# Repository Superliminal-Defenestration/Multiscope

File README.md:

Schematic Image

KiCad 3D Render

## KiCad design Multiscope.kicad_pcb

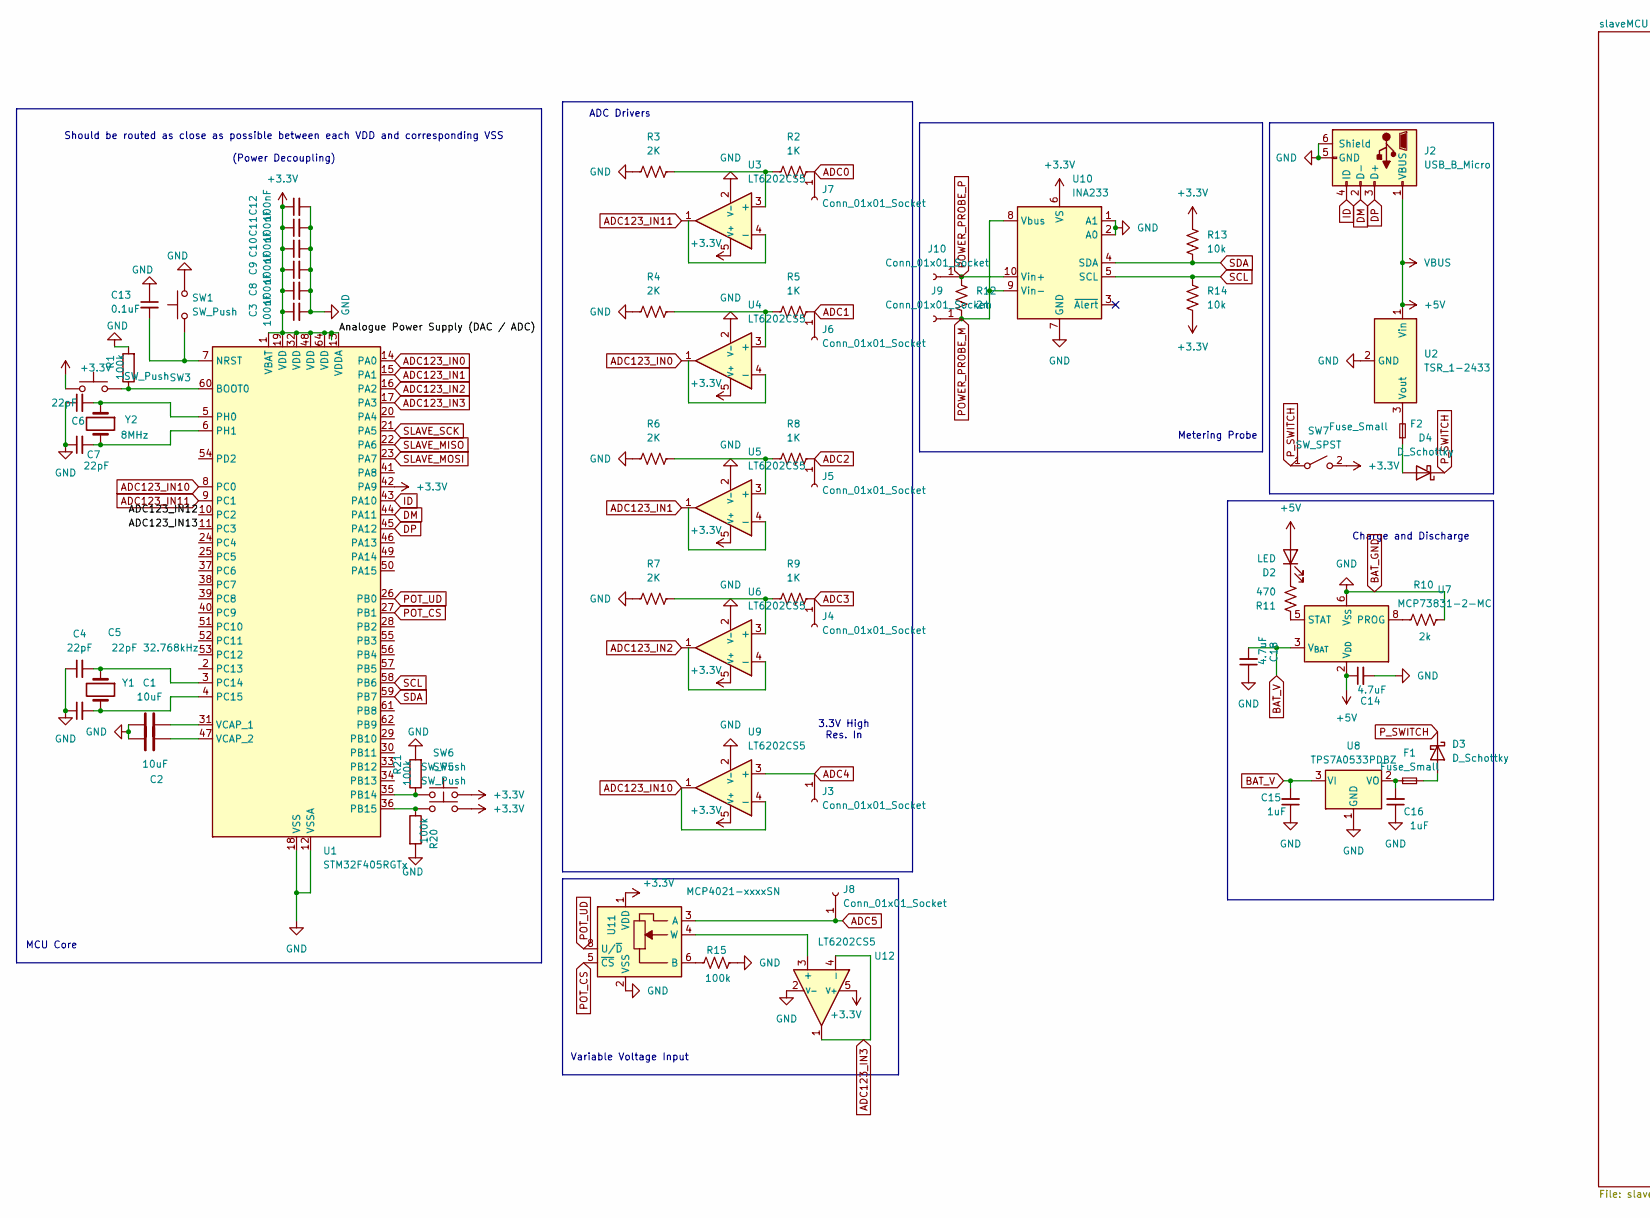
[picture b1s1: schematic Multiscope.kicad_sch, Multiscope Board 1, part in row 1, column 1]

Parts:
C1, C2: 10uF; C_Axial_L3.8mm_D2.6mm_P7.50mm_Horizontal
C3, C8, C9, C10, C11, C12: 100nF; C_Axial_L3.8mm_D2.6mm_P7.50mm_Horizontal
C4, C5, C6, C7: 22pF; C_Axial_L3.8mm_D2.6mm_P7.50mm_Horizontal
C13: 0.1uF; C_Axial_L3.8mm_D2.6mm_P7.50mm_Horizontal
C14, C18: 4.7uF; C_Axial_L3.8mm_D2.6mm_P7.50mm_Horizontal
C15, C16: 1uF; C_Axial_L3.8mm_D2.6mm_P7.50mm_Horizontal
D2: LED; LED_D8.0mm
D3, D4: D_Schottky; D_DO-15_P10.16mm_Horizontal
F1, F2: Fuse_Small; Fuse_Blade_Mini_directSolder
J2: USB_B_Micro; USB_Micro-AB_Molex_47590-0001
J3, J4, J5, J6, J7, J8, J9, J10: Conn_01x01_Socket; Banana_Jack_1Pin
R1, R15, R20, R21: 100k; R_Axial_DIN0204_L3.6mm_D1.6mm_P5.08mm_Horizontal
R2, R5, R8, R9: 1K; R_Axial_DIN0204_L3.6mm_D1.6mm_P5.08mm_Horizontal
R3, R4, R6, R7: 2K; R_Axial_DIN0204_L3.6mm_D1.6mm_P5.08mm_Horizontal
R10: 2k; R_Axial_DIN0204_L3.6mm_D1.6mm_P5.08mm_Horizontal
R11: 470; R_Axial_DIN0204_L3.6mm_D1.6mm_P5.08mm_Horizontal
R12: 2m; R_Axial_DIN0204_L3.6mm_D1.6mm_P5.08mm_Horizontal
R13, R14: 10k; R_Axial_DIN0204_L3.6mm_D1.6mm_P5.08mm_Horizontal
SW1, SW3, SW5, SW6: SW_Push; SW_PUSH_6mm
SW7: SW_SPST; SW_SPST_Omron_B3F-40xx
U1: STM32F405RGTx; LQFP-64_10x10mm_P0.5mm
U2: TSR_1-2433; Converter_DCDC_TRACO_TSR-1_THT
U3, U4, U5, U6, U9, U12: LT6202CS5; SOT-23-5
U7: MCP73831-2-MC; DFN-8-1EP_3x2mm_P0.5mm_EP1.7x1.4mm
U8: TPS7A0533PDBZ; SOT-23
U10: INA233; VSSOP-10_3x3mm_P0.5mm
U11: MCP4021-xxxxSN; SOIC-8_3.9x4.9mm_P1.27mm
Y1: 32.768kHz; Crystal_DS10_D1.0mm_L4.3mm_Vertical
Y2: 8MHz; Crystal_DS10_D1.0mm_L4.3mm_Vertical

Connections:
+5V: C14.1, D2.2 (A), J2.1 (VBUS), U2.1 (Vin), U7.1 (V_{DD}), U7.2 (V_{DD})
/ADC123_IN12: U1.10 (PC2)
/ADC123_IN13: U1.11 (PC3)
ADC0: J7.1, R2.2
ADC1: J6.1, R5.2
ADC2: J5.1, R8.2
ADC3: J4.1, R9.2
ADC4: J3.1, U9.3 (+)
ADC5: J8.1, U11.3 (A)
ADC123_IN0: U1.14 (PA0), U4.1
ADC123_IN1: U1.15 (PA1), U5.1
ADC123_IN2: U1.16 (PA2), U6.1
ADC123_IN3: U1.17 (PA3), U12.1, U12.4 (-)
ADC123_IN10: U1.8 (PC0), U9.1, U9.4 (-)
ADC123_IN11: U1.9 (PC1), U3.1
BAT_GND: C1.1, C2.1, C3.2, C4.1, C5.1, C6.1, C7.1, C8.2, C9.2, C10.2, C11.2, C12.2, C13.1, C14.2, C15.1, C16.1, C18.1, J2.5 (GND), J2.6 (Shield), R1.2, R3.1, R4.1, R6.1, R7.1, R10.2, R15.2, R20.2, R21.2, SW1.2, U1.12 (VSSA), U1.18 (VSS), U1.63 (VSS), U2.2 (GND), U3.2 (V-), U4.2 (V-), U5.2 (V-), U6.2 (V-), U7.6 (V_{SS}), U8.1 (GND), U9.2 (V-), U10.1 (A1), U10.2 (A0), U10.7 (GND), U11.2 (VSS), U12.2 (V-); also elsewhere on the board
BAT_V: C15.2, C18.2, U7.3 (V_{BAT}), U7.4 (V_{BAT}), U8.3 (VI)
DM: J2.2 (D-), U1.44 (PA11)
DP: J2.3 (D+), U1.45 (PA12)
ID: J2.4 (ID), U1.43 (PA10)
LED+: C3.1, C8.1, C9.1, C10.1, C11.1, C12.1, R13.1, R14.2, SW3.1, SW5.2, SW6.2, SW7.2 (B), U1.1 (VBAT), U1.13 (VDDA), U1.19 (VDD), U1.32 (VDD), U1.42 (PA9), U1.48 (VDD), U1.64 (VDD), U3.5 (V+), U4.5 (V+), U5.5 (V+), U6.5 (V+), U9.5 (V+), U10.6 (VS), U11.1 (VDD), U12.5 (V+); also elsewhere on the board
unnamed: D2.1 (K), R11.2
unnamed: D3.2 (A), F1.1
unnamed: D4.2 (A), F2.1
unnamed: R1.1, SW3.2, U1.60 (BOOT0)
unnamed: C13.2, SW1.1, U1.7 (NRST)
unnamed: R21.1, SW6.1, U1.35 (PB14)
unnamed: R20.1, SW5.1, U1.36 (PB15)
unnamed: C4.2, U1.3 (PC14), Y1.1
unnamed: C5.2, U1.4 (PC15), Y1.2
unnamed: C6.2, U1.5 (PH0), Y2.1
unnamed: C7.2, U1.6 (PH1), Y2.2
unnamed: C1.2, U1.31 (VCAP_1)
unnamed: C2.2, U1.47 (VCAP_2)
unnamed: F2.2, U2.3 (Vout)
unnamed: R2.1, R3.2, U3.3 (+)
unnamed: R4.2, R5.1, U4.3 (+)
unnamed: R6.2, R8.1, U5.3 (+)
unnamed: R7.2, R9.1, U6.3 (+)
unnamed: R10.1, U7.8 (PROG)
unnamed: R11.1, U7.5 (STAT)
unnamed: C16.2, F1.2, U8.2 (VO)
unnamed: R15.1, U11.6 (B)
unnamed: U11.4 (W), U12.3 (+)
POT_CS: U1.27 (PB1), U11.5 (~CS)
POT_UD: U1.26 (PB0), U11.8 (U/~D)
POWER_PROBE_P: J10.1, R12.1, U10.10 (Vin+)
P_SWITCH: D3.1 (K), D4.1 (K), SW7.1 (A)
SCL: R14.1, U1.58 (PB6), U10.5 (SCL)
SLAVE_MISO: U1.22 (PA6); also elsewhere on the board
SLAVE_MOSI: U1.23 (PA7); also elsewhere on the board
SLAVE_SCK: U1.21 (PA5); also elsewhere on the board

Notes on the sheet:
Metering Probe
ADC Drivers
3.3V High Res. In
Charge and Discharge
Variable Voltage Input
MCU Core
Should be routed as close as possible between each VDD and corresponding VSS (Power Decoupling)

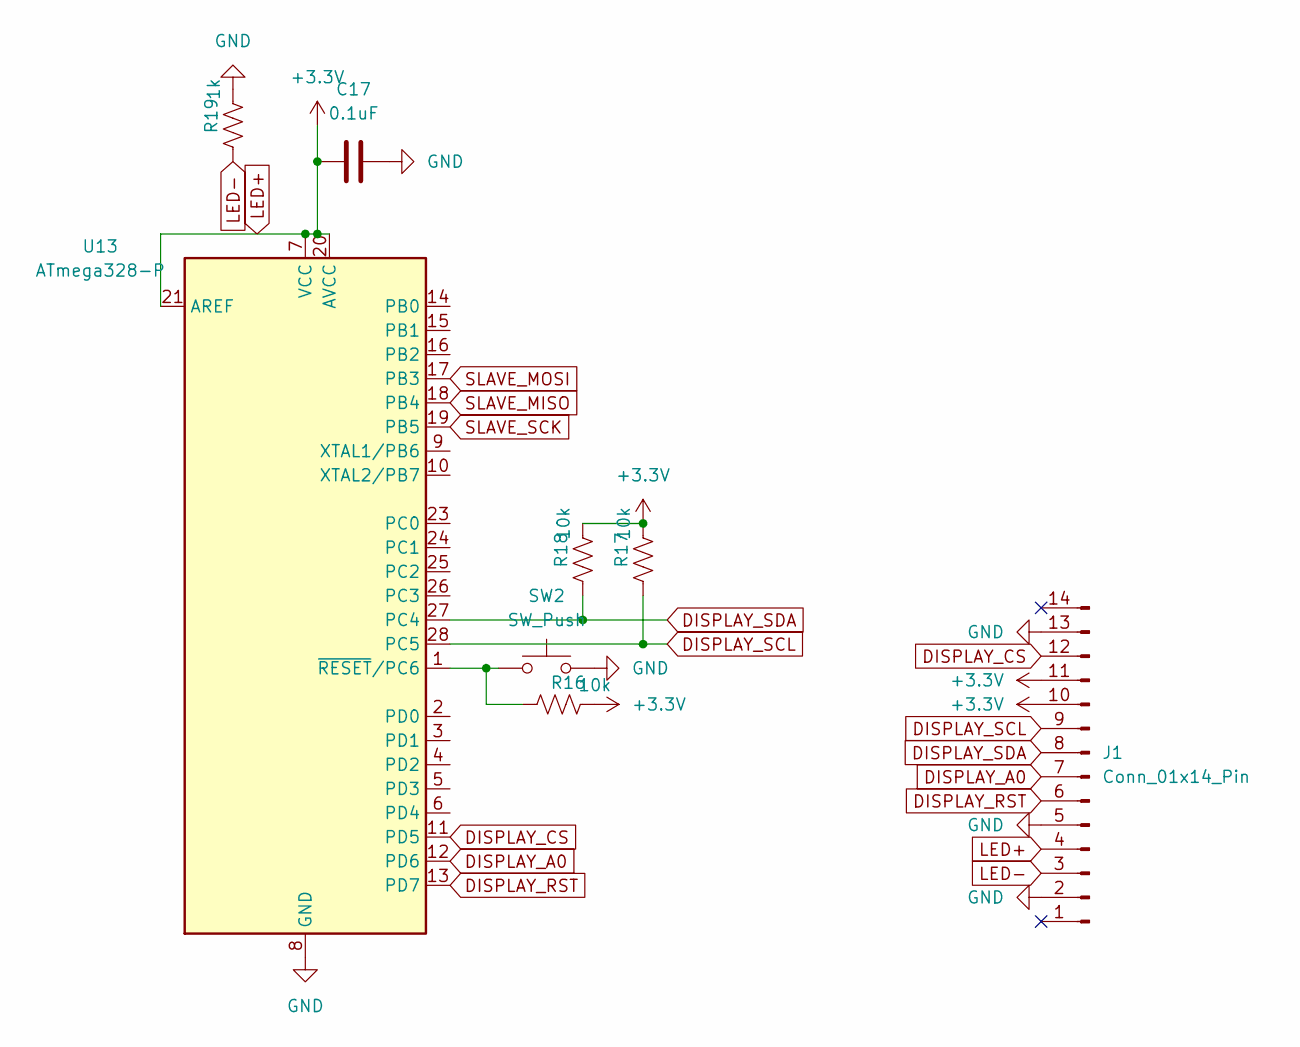
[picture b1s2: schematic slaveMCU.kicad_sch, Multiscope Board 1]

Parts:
C17: 0.1uF; C_Axial_L3.8mm_D2.6mm_P7.50mm_Horizontal
J1: Conn_01x14_Pin
R16, R17, R18: 10k; R_Axial_DIN0204_L3.6mm_D1.6mm_P5.08mm_Horizontal
R19: 1k; R_Axial_DIN0204_L3.6mm_D1.6mm_P5.08mm_Horizontal
SW2: SW_Push; SW_PUSH_6mm
U13: ATmega328-P; DIP-28_W7.62mm

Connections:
BAT_GND: C17.2, J1.2, J1.5, J1.13, R19.2, SW2.2, U13.8 (GND), U13.22 (GND); also elsewhere on the board
DISPLAY_A0: J1.7, U13.12 (PD6)
DISPLAY_CS: J1.12, U13.11 (PD5)
DISPLAY_RST: J1.6, U13.13 (PD7)
DISPLAY_SCL: J1.9, R17.1, U13.28 (PC5)
DISPLAY_SDA: J1.8, R18.1, U13.27 (PC4)
LED+: C17.1, J1.4, J1.10, J1.11, R16.2, R17.2, R18.2, U13.7 (VCC), U13.20 (AVCC), U13.21 (AREF); also elsewhere on the board
LED-: J1.3, R19.1
unnamed: R16.1, SW2.1, U13.1 (~RESET/PC6)
SLAVE_MISO: U13.18 (PB4); also elsewhere on the board
SLAVE_MOSI: U13.17 (PB3); also elsewhere on the board
SLAVE_SCK: U13.19 (PB5); also elsewhere on the board

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
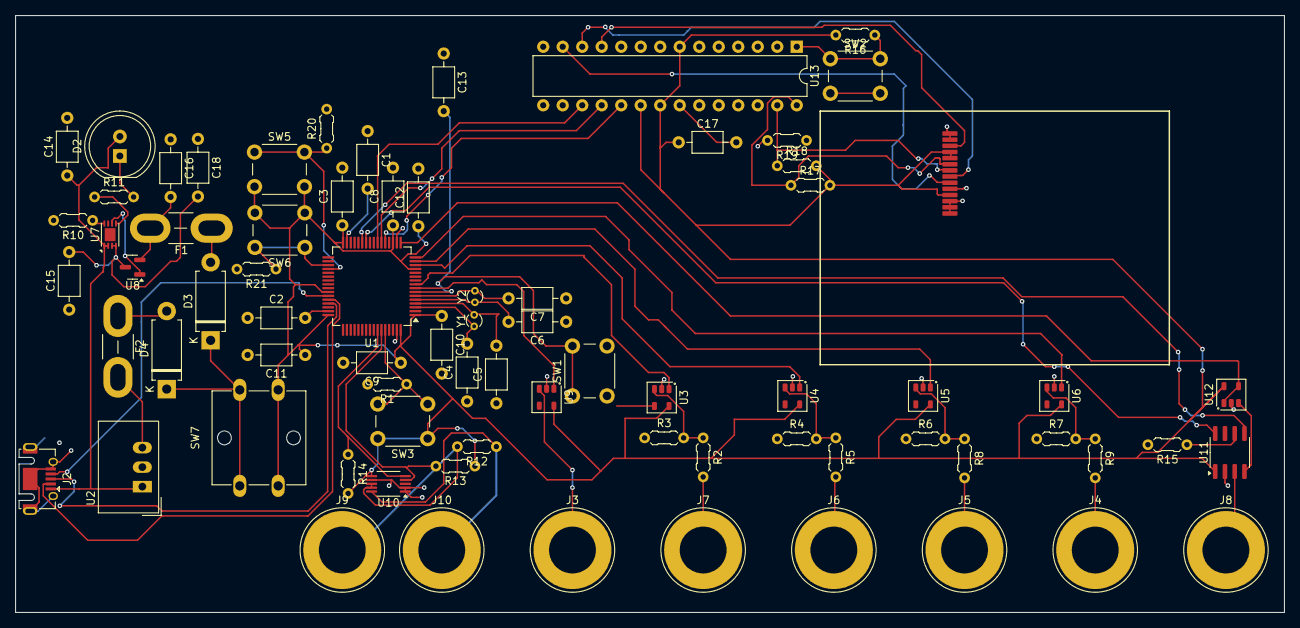
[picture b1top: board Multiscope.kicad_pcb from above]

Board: 2 copper layers, 165.2 x 77.7 mm, 74 parts (0 on the bottom side), 54 nets.

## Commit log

2025-09-10 init
2025-09-10 Licensing
2025-09-10 setup i2c interface to metering ic
2025-09-25 added slave MCU, added proper power Auto-OR-ing (uses Schottkys), added variable v-supply input
2025-10-06 layout started
2025-10-27 Laid out traces for display
2025-10-27 Update README with additional images
    Added schematic, KiCad 3D render, and fabrication images.
2025-10-27 Remove fabrication/layout image from README
    Removed fabrication/layout image from README.

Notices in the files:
Multiscope.kicad_sch:
Provided under CERN-OHL-S-2.0
